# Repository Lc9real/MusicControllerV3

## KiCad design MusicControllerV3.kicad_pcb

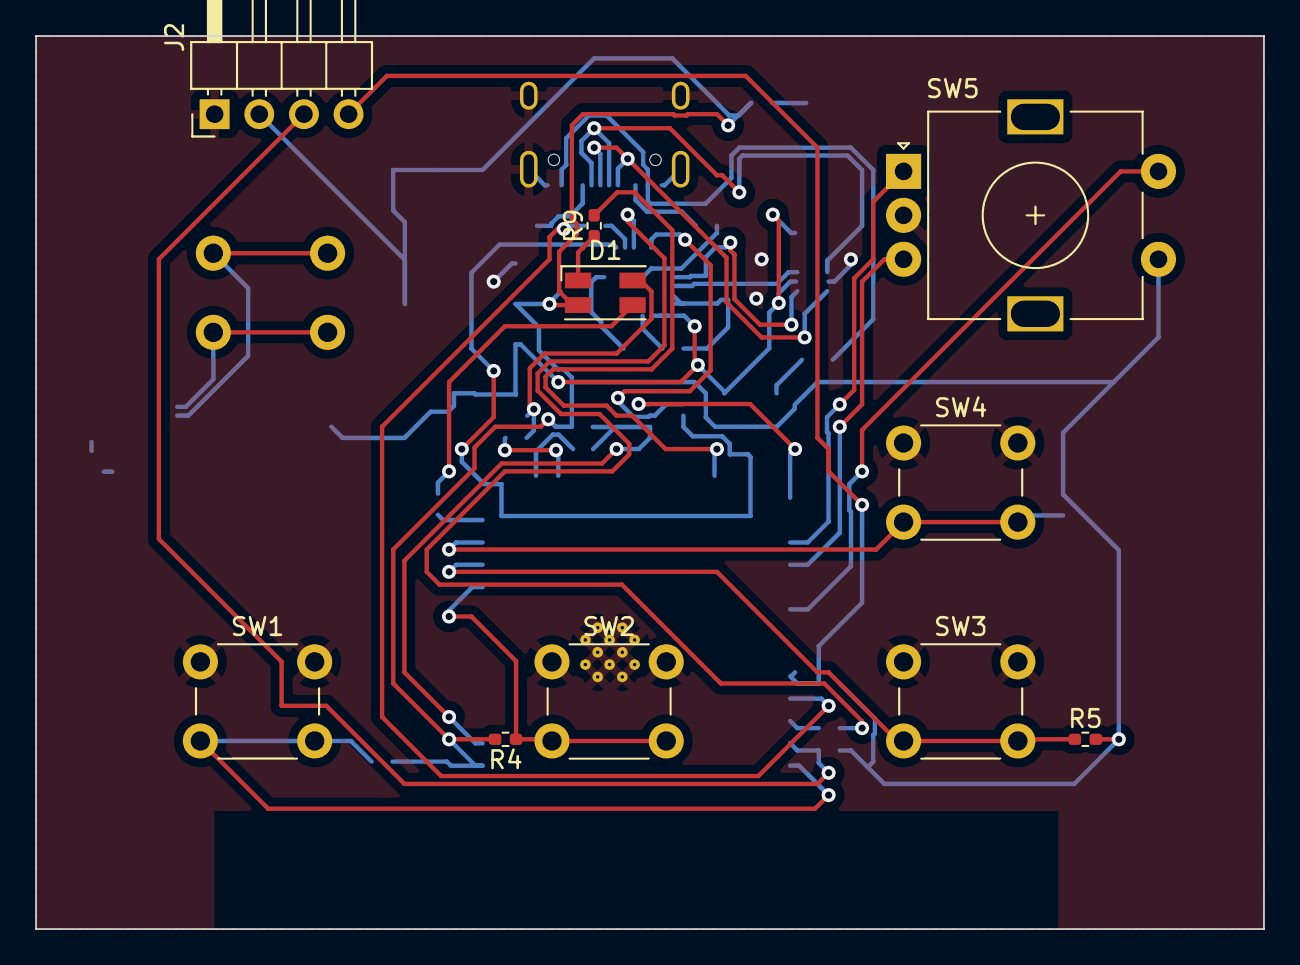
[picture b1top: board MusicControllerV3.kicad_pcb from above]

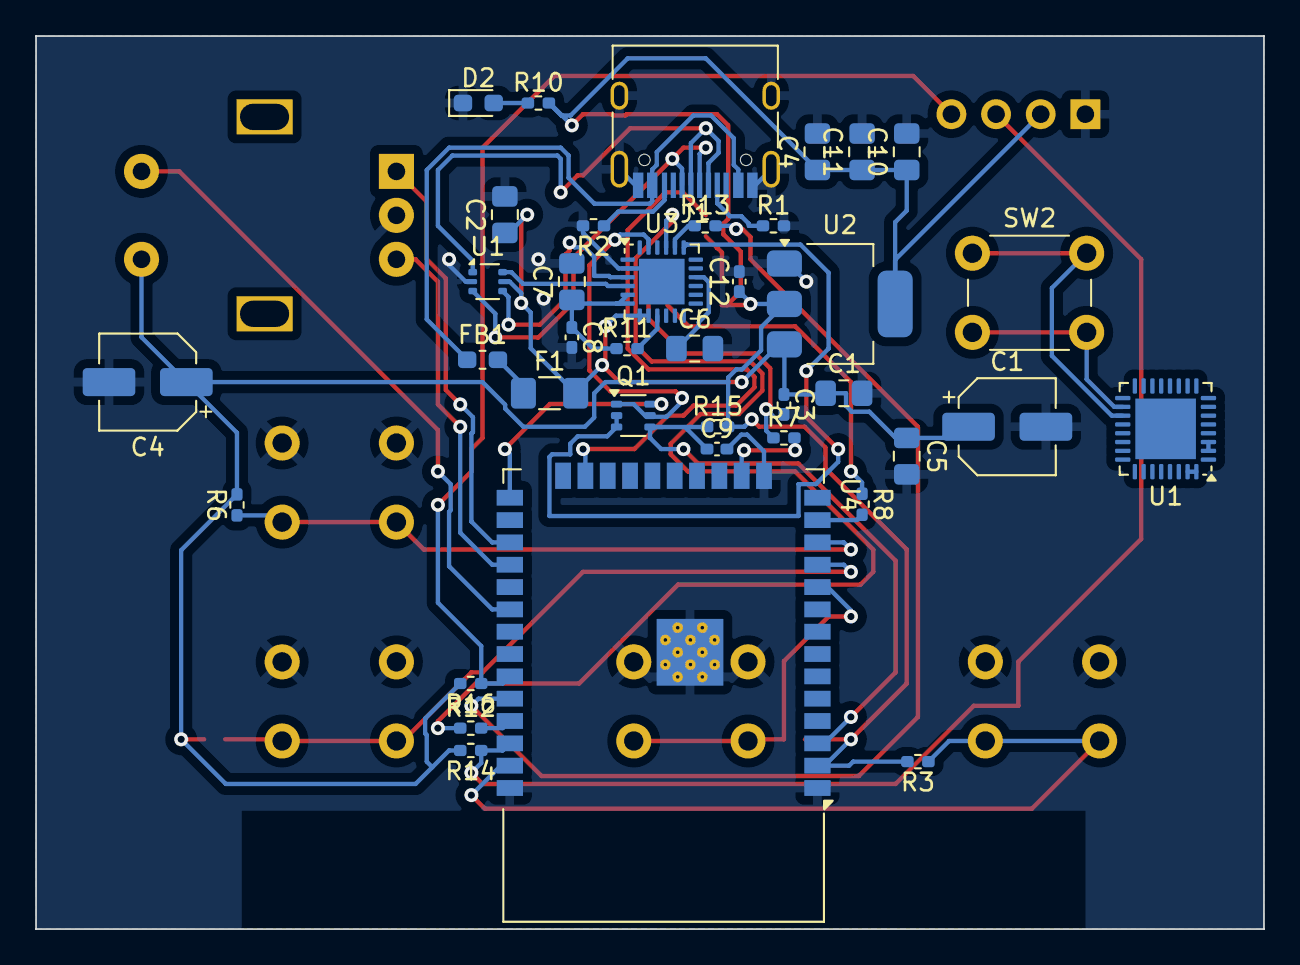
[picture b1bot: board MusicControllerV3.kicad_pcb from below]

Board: 2 copper layers, 69.8 x 50.8 mm, 48 parts (38 on the bottom side), 42 nets.

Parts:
C1, C4: 22u; CP_Elec_5x5.4
C1#2, C2, C4#2, C7, C10, C11: 22u; C_0805_2012Metric_Pad1.18x1.45mm_HandSolder
C3, C8, C9, C12: 100n; C_0402_1005Metric_Pad0.74x0.62mm_HandSolder
C5, C6: 4u7; C_0805_2012Metric_Pad1.18x1.45mm_HandSolder
D1: LED_RGBA; LED_RGB_Wuerth-PLCC4_3.2x2.8mm_150141M173100
D2: LED; LED_0603_1608Metric_Pad1.05x0.95mm_HandSolder
F1: Polyfuse_1A; Fuse_1206_3216Metric_Pad1.42x1.75mm_HandSolder
FB1: BLM21PG221; L_0603_1608Metric_Pad1.05x0.95mm_HandSolder
J1: USB_C_Receptacle_USB2.0_16P; USB_C_Receptacle_HRO_TYPE-C-31-M-12
J2: Conn_01x04; PinHeader_1x04_P2.54mm_Horizontal
Q1: UMH3N; SOT-363_SC-70-6
R1, R2: 5k1; R_0402_1005Metric_Pad0.72x0.64mm_HandSolder
R3, R4, R5, R6, R14, R16: 4k7; R_0402_1005Metric_Pad0.72x0.64mm_HandSolder
R7, R8, R9, R10: 1K; R_0402_1005Metric_Pad0.72x0.64mm_HandSolder
R11: 10K; R_0402_1005Metric_Pad0.72x0.64mm_HandSolder
R12, R13: 22R; R_0402_1005Metric_Pad0.72x0.64mm_HandSolder
R15: 10k; R_0402_1005Metric_Pad0.72x0.64mm_HandSolder
SW1, SW2, SW3, SW4: SW_SPST; SW_PUSH_6mm_H4.3mm
SW2#2: SW_Push; SW_PUSH_6mm
SW5: RotaryEncoder_Switch; RotaryEncoder_Alps_EC11E-Switch_Vertical_H20mm
U1: ESP32-C3; QFN-32-1EP_5x5mm_P0.5mm_EP3.45x3.45mm
U1#2: USBLC6-2P6; SOT-666
U2: LM1117MP-3.3; SOT-223-3_TabPin2
U3: CP2104; QFN-24-1EP_4x4mm_P0.5mm_EP2.6x2.6mm
U4: ESP32-WROOM-32D

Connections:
+3.3V: C4.1, C4#2.1, C10.1, C11.1, C12.1, D1.4 (A), J2.2, R3.2, R4.2, R5.2, R6.2, R10.2, R14.2, R15.2, R16.2, SW5.S1, U2.2 (VO), U4.2 (VDD)
+3.3VA: C7.1, C8.1, R11.1, U3.5 (VIO), U3.6 (VDD)
+5V: C1.1, C1#2.1, C2.1, C3.1, C5.1, F1.2, U1#2.5 (VBUS), U2.3 (VI), U3.7 (REGIN), U3.8 (VBUS)
+5VP: FB1.1, J1.A4 (VBUS), J1.A9 (VBUS), J1.B4 (VBUS), J1.B9 (VBUS)
/Button1: R3.1, SW1.2 (B), U4.37 (IO23)
/Button2: R4.1, SW2.2 (B), U4.10 (IO25)
/Button3: R5.1, SW3.2 (B), U4.11 (IO26)
/Button4: R6.1, SW4.2 (B), U4.12 (IO27)
/DTR: Q1.1 (E1), Q1.5 (B2), U3.23 (~DTR)
/EN: C9.1, Q1.4 (E2), R15.1, U4.3 (EN)
/IO0: Q1.6 (C1), U4.25 (IO0)
/LED_B: R9.2, U4.23 (IO15)
/LED_G: R8.2, U4.13 (IO14)
/LED_R: R7.2, U4.16 (IO13)
/RTS: Q1.2 (B1), Q1.3 (C2), U3.19 (~RTS)
/RX: R12.2, U4.35 (TXD0/IO1)
/RotaryCLK: SW5.A, U4.27 (IO16)
/RotaryDT: SW5.B, U4.28 (IO17)
/RotaryEncoderSwitch: SW5.S2, U4.30 (IO18)
/SCL: J2.3, R14.1, U4.36 (IO22)
/SDA: J2.4, R16.1, U4.33 (IO21)
/TX: R13.2, U4.34 (RXD0/IO3)
GND: C1.2, C1#2.2, C2.2, C3.2, C4.2, C4#2.2, C5.2, C6.2, C7.2, C8.2, C9.2, C10.2, C11.2, C12.2, D2.1 (K), J1.A1 (GND), J1.A12 (GND), J1.B1 (GND), J1.B12 (GND), J1.S1 (SHIELD), J2.1, R1.2, R2.2, SW1.1 (A), SW2.1 (A), SW3.1 (A), SW4.1 (A), SW5.C, U1#2.2 (GND), U2.1 (GND), U3.2 (GND), U3.25 (GND), U4.1 (GND), U4.15 (GND), U4.38 (GND), U4.39 (GND)
unnamed: D1.3 (BK), R9.1
unnamed: D1.2 (GK), R8.1
unnamed: D1.1 (RK), R7.1
unnamed: D2.2 (A), R10.1
unnamed: F1.1, FB1.2
unnamed: J1.A5 (CC1), R1.1
unnamed: J1.B5 (CC2), R2.1
unnamed: J1.A6 (D+), J1.B6 (D+), U1#2.3 (I/O2)
unnamed: J1.A7 (D-), J1.B7 (D-), U1#2.1 (I/O1)
unnamed: SW2#2.1, U1.19 (SPIHD/GPIO12)
unnamed: U1.2 (VDD3P3), U1.3 (VDD3P3)
unnamed: U1.31 (VDDA), U1.32 (VDDA)
unnamed: SW2#2.2, U1.18 (VDD_SPI/GPIO11)
unnamed: U1#2.4 (I/O2), U3.3 (D+)
unnamed: U1#2.6 (I/O1), U3.4 (D-)
unnamed: R13.1, U3.20 (RXD)
unnamed: R12.1, U3.21 (TXD)
unnamed: C6.1, U3.16 (VPP)
unnamed: R11.2, U3.9 (~RST)

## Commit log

2024-12-06 initial
